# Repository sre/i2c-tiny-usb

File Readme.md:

# I²C Tiny USB

This is my variant of i2c-tiny-usb from Dr. Till Harbaum. You
can find the original project on his homepage:

http://www.harbaum.org/till/i2c_tiny_usb/index.shtml

I modified the PCB schematics to fit my requirements and created
a nice case for it. The actual firmware for the ATtiny is exactly
the same. Instead of the ATtiny45 I used an ATtiny85, since it's
cheaper nowadays.

The PCB and the case are licensed under CC-BY 3.0:

https://creativecommons.org/licenses/by/3.0/

# Images

-- Sebastian Reichel <sre@ring0.de>

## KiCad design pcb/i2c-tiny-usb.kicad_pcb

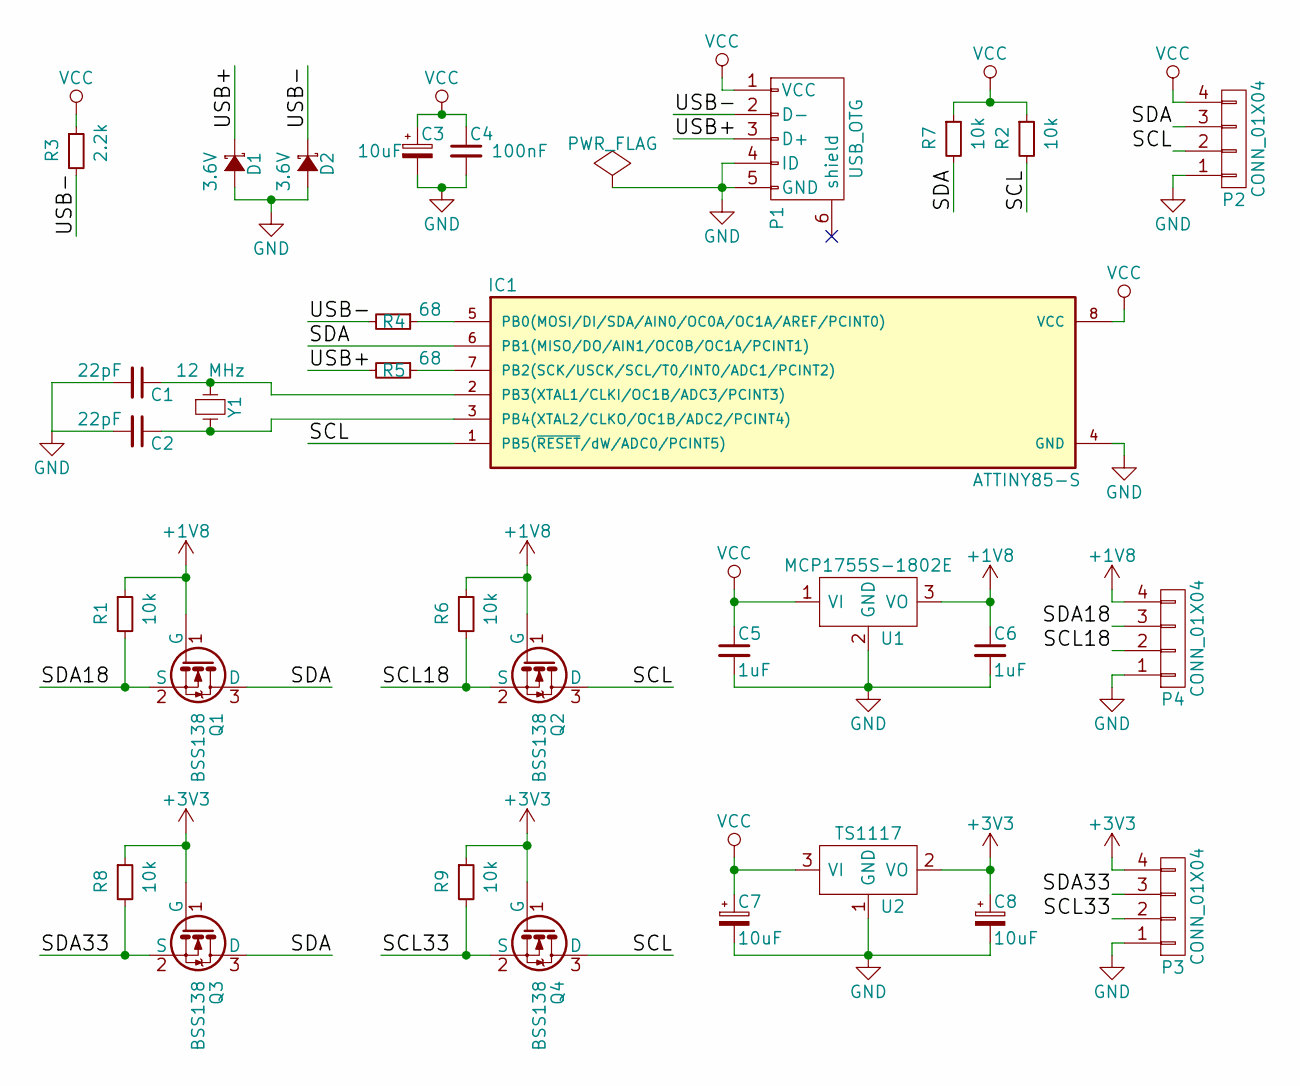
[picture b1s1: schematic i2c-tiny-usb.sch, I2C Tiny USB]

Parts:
C1, C2: 22pF; C_0805
C3: 10uF; TantalC_SizeA_EIA-3216_Wave
C4: 100nF; C_0805
C5, C6: 1uF; C_0805
C7, C8: 10uF; C_0805
D1, D2: 3.6V; MiniMELF_Standard
IC1: ATTINY85-S; SOIC-8-JEITA
P1: USB_OTG; USB_Mini-B
P2, P3, P4: CONN_01X04; Pin_Header_Angled_1x04
Q1, Q2, Q3, Q4: BSS138; SOT-23
R1, R2, R6, R7, R8, R9: 10k; R_0805
R3: 2.2k; R_0805
R4, R5: 68; R_0805
U1: MCP1755S-1802E; SOT-223
U2: TS1117; SOT-223
Y1: 12 MHz; Crystal_HC49-SD_SMD

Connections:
+1V8: C6.1, P4.4, Q1.1 (G), Q2.1 (G), R1.1, R6.1, U1.3 (VO)
+3V3: C8.1, P3.4, Q3.1 (G), Q4.1 (G), R8.1, R9.1, U2.2 (VO)
/SCL: IC1.1 (PB5(~RESET~/dW/ADC0/PCINT5)), P2.2, Q2.3 (D), Q4.3 (D), R2.2
/SCL18: P4.2, Q2.2 (S), R6.2
/SCL33: P3.2, Q4.2 (S), R9.2
/SDA: IC1.6 (PB1(MISO/DO/AIN1/OC0B/OC1A/PCINT1)), P2.3, Q1.3 (D), Q3.3 (D), R7.2
/SDA18: P4.3, Q1.2 (S), R1.2
/SDA33: P3.3, Q3.2 (S), R8.2
/USB+: D1.1 (K), P1.3 (D+), R5.2
/USB-: D2.1 (K), P1.2 (D-), R3.2, R4.2
GND: C1.2, C2.2, C3.2, C4.2, C5.2, C6.2, C7.2, C8.2, D1.2 (A), D2.2 (A), IC1.4 (GND), P1.4 (ID), P1.5 (GND), P2.1, P3.1, P4.1, U1.2 (GND), U2.1 (GND)
unnamed: C1.1, IC1.2 (PB3(XTAL1/CLKI/OC1B/ADC3/PCINT3)), Y1.1
unnamed: C2.1, IC1.3 (PB4(XTAL2/CLKO/OC1B/ADC2/PCINT4)), Y1.2
unnamed: IC1.5 (PB0(MOSI/DI/SDA/AIN0/OC0A/OC1A/AREF/PCI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), R4.1
unnamed: IC1.7 (PB2(SCK/USCK/SCL/T0/INT0/ADC1/PCINT2)), R5.1
VCC: C3.1, C4.1, C5.1, C7.1, IC1.8 (VCC), P1.1 (VCC), P2.4, R2.1, R3.1, R7.1, U1.1 (VI), U2.3 (VI)

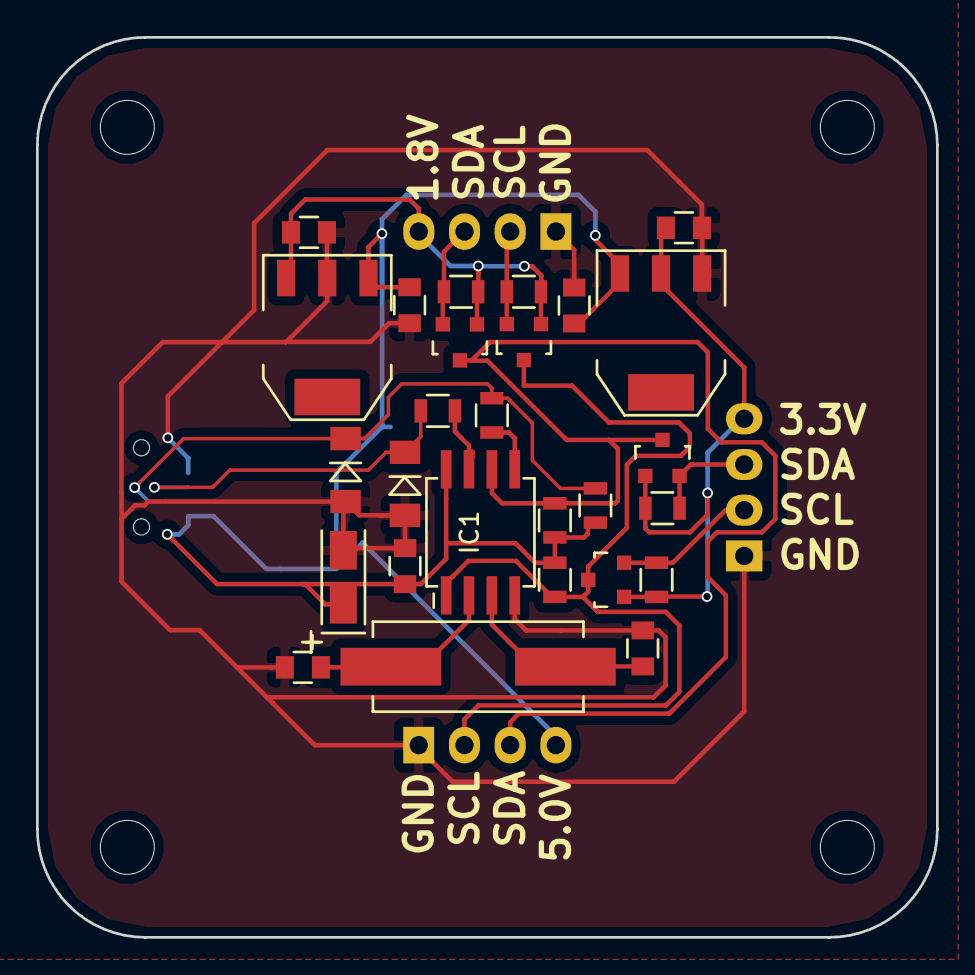
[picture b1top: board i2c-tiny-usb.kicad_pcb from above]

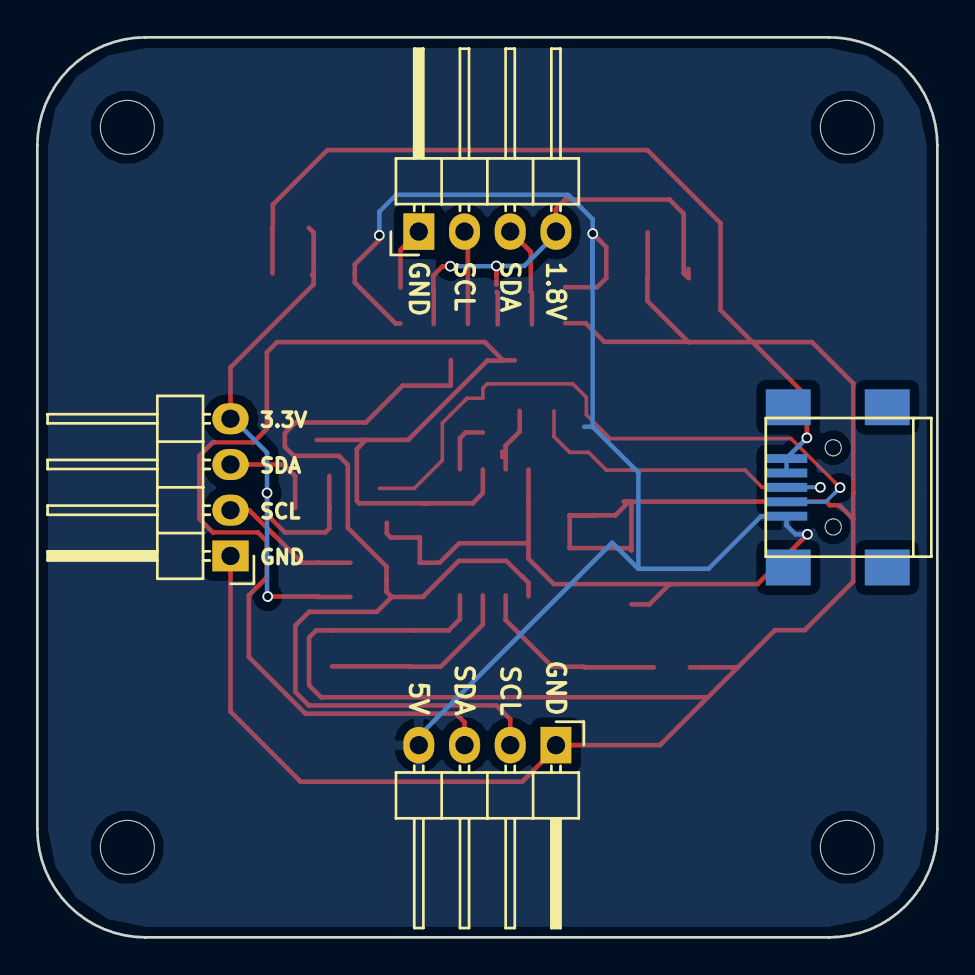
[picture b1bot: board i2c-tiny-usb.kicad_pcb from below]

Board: 2 copper layers, 50.0 x 50.0 mm, 31 parts (4 on the bottom side), 16 nets.

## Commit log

2016-12-10 add case design
2016-12-10 initial pcb design
2016-12-10 add gerber files
2016-12-10 add firmware
2016-12-10 add some images
2016-12-10 add readme
2019-07-29 Add photo from pcb + case
